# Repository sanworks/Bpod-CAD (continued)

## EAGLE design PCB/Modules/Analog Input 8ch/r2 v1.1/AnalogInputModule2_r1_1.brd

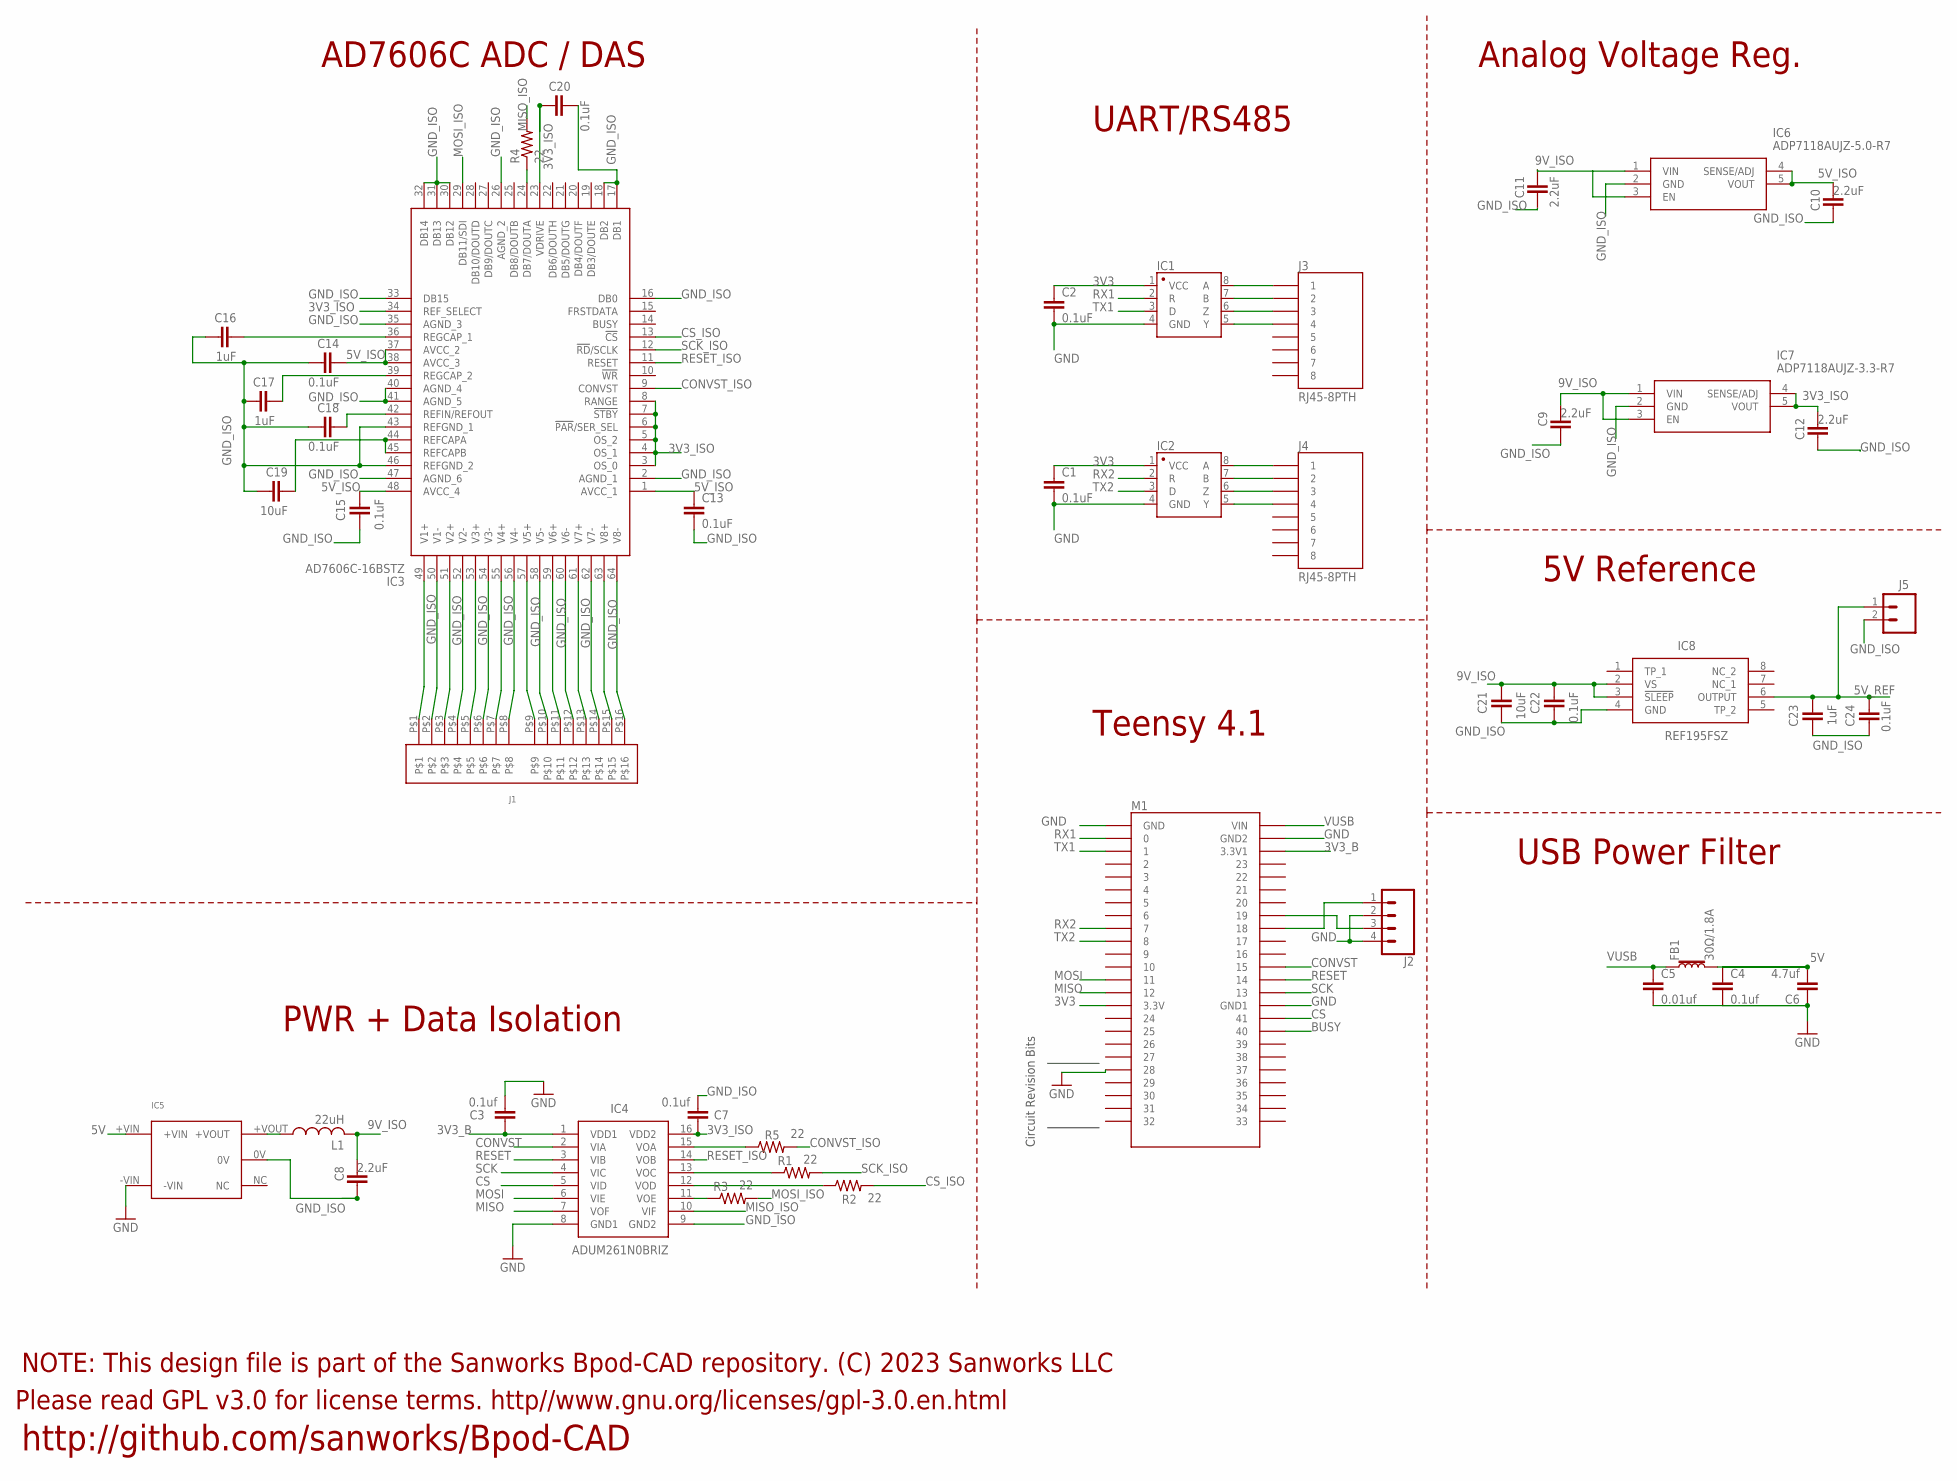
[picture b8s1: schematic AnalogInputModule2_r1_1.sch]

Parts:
C1, C2, C13, C14, C15, C18, C20, C22, C24: 0.1uF; 0805
C3, C4, C7: 0.1uf; 0805
C5: 0.01uf; 0805
C6: 4.7uf; 1206@2
C8, C9, C10, C11, C12: 2.2uF; 0805
C16, C17, C23: 1uF; 0805
C19, C21: 10uF; 0805
FB1: 30Ω/1.8A; 0603
IC1, IC2: SN65HVD31DR; SO08
IC3: AD7606C-16BSTZ; QFP50P1200X1200X160-64N
IC4: ADUM261N0BRIZ; SOIC127P1030X264-16N
IC5: 5V; MTU1D0505MC
IC6: ADP7118AUJZ-5.0-R7; SOT95P280X100-5N
IC7: ADP7118AUJZ-3.3-R7; SOT95P280X100-5N
IC8: REF195FSZ; SOIC127P600X175-8N
J1: 16POS_MOLEX_SOCKET
J2: CONN_04SCREW_LOCK; SCREWTERMINAL-3.5MM-4_LOCK
J3, J4: RJ45-8PTH; RJ45-8
J5: CONN_023.5MM_LOCK; SCREWTERMINAL-3.5MM-2_LOCK
L1: 22uH; L3225M
M1: TEENSY4.1_SIDESONLY
R1, R2, R3, R4, R5: 22; R0805

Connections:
3V3: C1.1, C2.1, IC1.1 (VCC), IC2.1 (VCC), M1.3V3 (3.3V)
3V3_B: C3.1, IC4.1 (VDD1), M1.3V3_LO (3.3V1)
3V3_ISO: C7.1, C12.2, C20.1, IC3.3 (OS_0), IC3.4 (OS_1), IC3.5 (OS_2), IC3.6 (!PAR!/SER_SEL), IC3.7 (!STBY), IC3.8 (RANGE), IC3.23 (VDRIVE), IC3.34 (REF_SELECT), IC4.16 (VDD2), IC7.4 (SENSE/ADJ), IC7.5 (VOUT)
5V: C4.1, C6.2, FB1.2, IC5.+VIN
5V_ISO: C10.2, C13.1, C14.2, C15.2, IC3.1 (AVCC_1), IC3.37 (AVCC_2), IC3.38 (AVCC_3), IC3.48 (AVCC_4), IC6.4 (SENSE/ADJ), IC6.5 (VOUT)
5V_REF: C23.2, C24.2, IC8.6 (OUTPUT), J5.1
9V_ISO: C8.2, C9.2, C11.2, C21.2, C22.2, IC6.1 (VIN), IC6.3 (EN), IC7.1 (VIN), IC7.3 (EN), IC8.2 (VS), IC8.3 (!SLEEP), L1.2
BUSY: M1.40
CONVST: IC4.2 (VIA), M1.15/A1 (15)
CONVST_ISO: IC3.9 (CONVST), R5.2
CS: IC4.5 (VID), M1.41
CS_ISO: IC3.13 (!CS), R2.2
GND: C1.2, C2.2, C3.2, C4.2, C5.2, C6.1, IC1.4 (GND), IC2.4 (GND), IC4.8 (GND1), IC5.-VIN, J2.2, J2.4, M1.28, M1.AGND (GND), M1.GND (GND1), M1.GND1 (GND2)
GND_ISO: C7.2, C8.1, C9.1, C10.1, C11.1, C12.1, C13.2, C14.1, C15.1, C16.1, C17.1, C18.1, C19.1, C20.2, C21.1, C22.1, C23.1, C24.1, IC3.2 (AGND_1), IC3.16 (DB0), IC3.17 (DB1), IC3.18 (DB2), IC3.26 (AGND_2), IC3.30 (DB12), IC3.31 (DB13), IC3.32 (DB14), IC3.33 (DB15), IC3.35 (AGND_3), IC3.40 (AGND_4), IC3.41 (AGND_5), IC3.43 (REFGND_1), IC3.46 (REFGND_2), IC3.47 (AGND_6), IC3.50 (V1-), IC3.52 (V2-), IC3.54 (V3-), IC3.56 (V4-), IC3.58 (V5-), IC3.60 (V6-), IC3.62 (V7-), IC3.64 (V8-), IC4.9 (GND2), IC5.0V, IC6.2 (GND), IC7.2 (GND), IC8.4 (GND), J1.P$2, J1.P$4, J1.P$6, J1.P$8, J1.P$10, J1.P$12, J1.P$14, J1.P$16, J5.2
MISO: IC4.7 (VOF), M1.12/MISO (12)
MISO_ISO: IC4.10 (VIF), R4.2
MOSI: IC4.6 (VIE), M1.11/MOSI (11)
MOSI_ISO: IC3.29 (DB11/SDI), R3.2
unnamed: IC1.6 (Z), J3.3
unnamed: IC1.8 (A), J3.1
unnamed: IC1.5 (Y), J3.4
unnamed: IC1.7 (B), J3.2
unnamed: IC2.6 (Z), J4.3
unnamed: IC2.5 (Y), J4.4
unnamed: IC2.8 (A), J4.1
unnamed: IC2.7 (B), J4.2
unnamed: IC3.63 (V8+), J1.P$15
unnamed: IC3.61 (V7+), J1.P$13
unnamed: IC3.59 (V6+), J1.P$11
unnamed: IC3.57 (V5+), J1.P$9
unnamed: IC3.55 (V4+), J1.P$7
unnamed: IC3.53 (V3+), J1.P$5
unnamed: IC3.51 (V2+), J1.P$3
unnamed: IC3.49 (V1+), J1.P$1
unnamed: IC4.13 (VOC), R1.1
unnamed: IC4.12 (VOD), R2.1
unnamed: IC4.11 (VOE), R3.1
unnamed: IC3.24 (DB7/DOUTA), R4.1
unnamed: IC4.15 (VOA), R5.1
unnamed: C16.2, IC3.36 (REGCAP_1)
unnamed: C17.2, IC3.39 (REGCAP_2)
unnamed: C18.2, IC3.42 (REFIN/REFOUT)
unnamed: C19.2, IC3.44 (REFCAPA), IC3.45 (REFCAPB)
unnamed: J2.1, M1.18/A4/SDA (18)
unnamed: IC5.+VOUT, L1.1
unnamed: J2.3, M1.19/A5/SCL (19)
RESET: IC4.3 (VIB), M1.14/A0 (14)
RESET_ISO: IC3.11 (RESET), IC4.14 (VOB)
RX1: IC1.2 (R), M1.0/RX (0)
RX2: IC2.2 (R), M1.7
SCK: IC4.4 (VIC), M1.13/SCK (13)
SCK_ISO: IC3.12 (!RD!/SCLK), R1.2
TX1: IC1.3 (D), M1.1/TX (1)
TX2: IC2.3 (D), M1.8
VUSB: C5.1, FB1.1, M1.VIN

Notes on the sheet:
Teensy 4.1
UART/RS485
USB Power Filter
AD7606C ADC / DAS
PWR + Data Isolation
Analog Voltage Reg.
5V Reference
Please read GPL v3.0 for license terms. http//www.gnu.org/licenses/gpl-3.0.en.html
NOTE: This design file is part of the Sanworks Bpod-CAD repository. (C) 2023 Sanworks LLC
http://github.com/sanworks/Bpod-CAD
Circuit Revision Bits

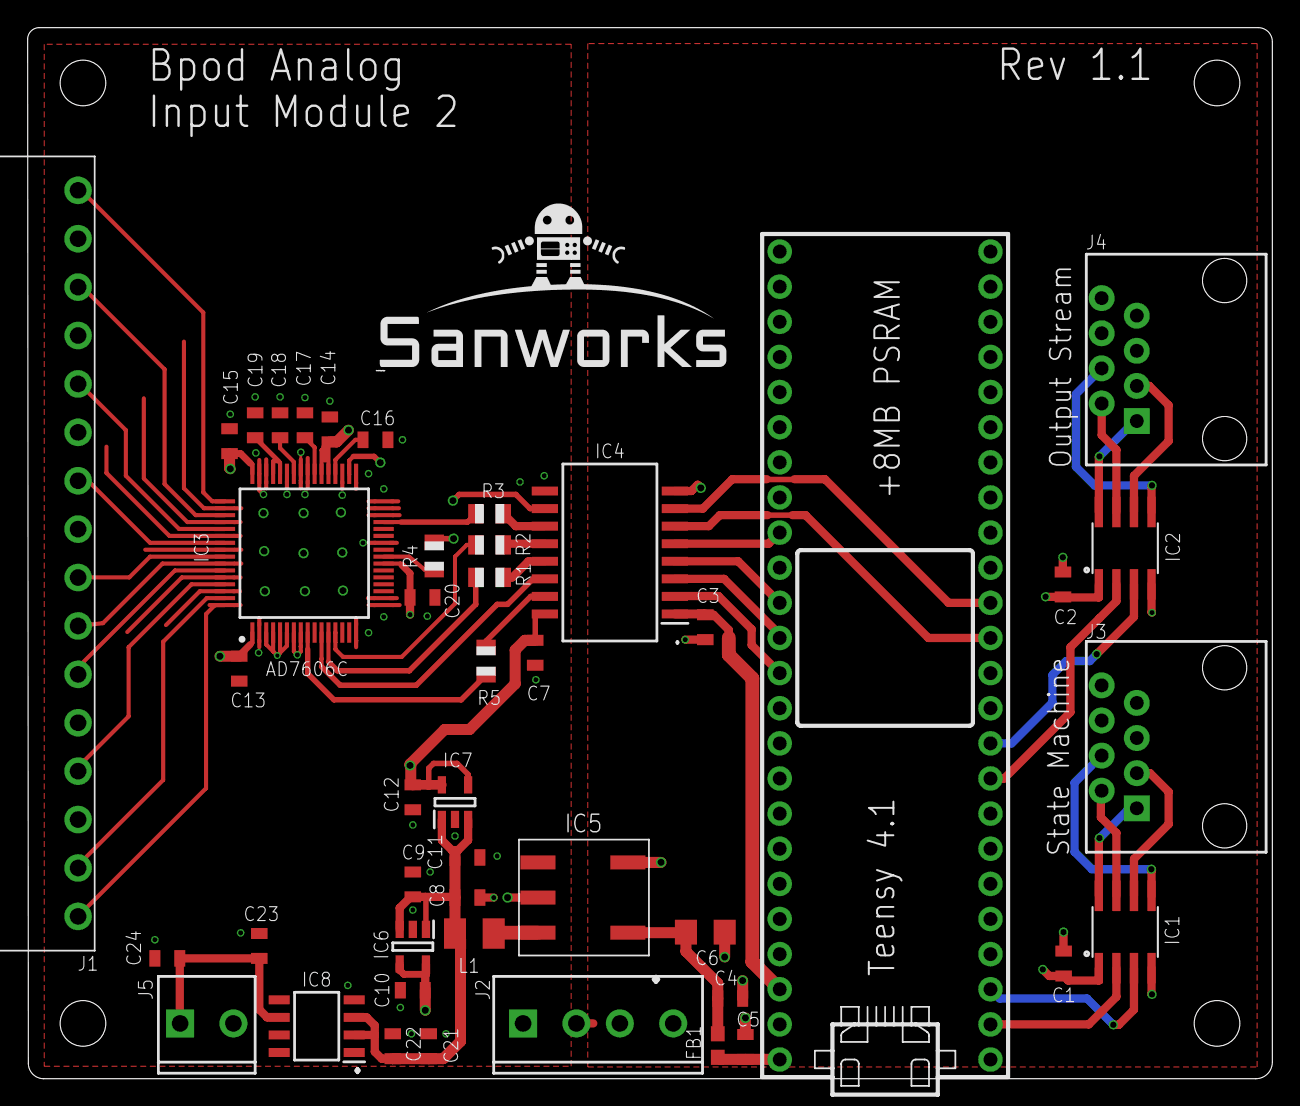
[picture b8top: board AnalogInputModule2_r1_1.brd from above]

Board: 4 copper layers, 90.0 x 76.0 mm, 50 parts (0 on the bottom side), 54 nets.

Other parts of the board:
U$1: SANWORKS_LOGO
U$5, U$6, U$7, U$8: STAND-OFF

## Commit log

2016-11-23 -Initial commit. CAD designs were previously part of the Bpod master repository.
2016-12-20 -Reorganized modules (to separate v0.5, v0.7) -Added Bpod Arduino shield for v0.7
2017-01-20 -Improved mouse box floor: increased margin between slits and floor edge, and rounded sharp corners for added mechanical strength
2017-02-01 -Added design files (PCB and enclosure) for 4-channel analog output module
2017-02-10 -Improved Analog Output Module schematic organization and labeling -Thickened trace connecting Analog Output Module ground planes
2017-03-07 -Added design files for the Pocket State Machine - a new state machine module with many improvements, based on Teensy 3.6. -Added design files for isolated valve driver module -Added new revision of 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
2017-03-07 -Added lickometer design adapted for 15-gage tubing, with sheath to protect the sensors -Added 3D printable sheets to protect bottoms of valve driver and pocket state machine boards
2017-03-08 -Added Bpod state machine PCB r0.8. Identical to r0.7 but adds isolation for BNC TTL output channels.
2017-03-10 -Updated silk screen, improved trace clearance and reorganized schematic for ValveModule PCB
2017-04-07 -Added DDS Module PCB design -Changed engraved label for clarification on analog output module enclosure
2017-04-09 -Updated analog output module PCB design
2017-04-12 -Added SNES Module PCB design -Added SNES Module bottom-guard design -Added DDS Module enclosure -Updated link to Bpod-CAD repository in schematic files
2017-05-02 - Added 8-channel analog output PCB - Updated I2C module PCB - Reorganized repository to put PCB bottom insulator designs in 1 folder -
2017-05-05 -Added improved lickometer design
2017-05-11 -Updated lickometer design, with sheath capable of mounting to a 6mm ThorLabs post.
2017-05-11 -Updated lickometer STL files
2017-07-05 -Updated 8-ch analog output module enclosure -Updated DDS module enclosure -Added 8-ch analog input module enclosure -Added 8-ch analog input module PCB
2017-07-07 -Updated DDS module PCB design. New design allows full-scale amplitude control, and has fewer components.
2017-07-10 -Added Bpod state machine r0.9 PCB files. r0.9 changes the optical isolator IC (which had been discontinued). A decoupling capacitor was added to each new optoisolator. The optoisolator series resist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
2017-08-03 -Added rotary encoder module PCB -Added 3D printable ThorLabs mount and paw-manipulation wheels for rotary encoder
2017-08-15 -Revised lickometer CAD files to improve 3D printing outcomes -Added interface board mount for 5mm acrylic (requires longer M4 screws; 20mm length up from 16mm)
2017-09-13 -Critical Update for modules with optional RJ45 power (ValveDriver, I2C, SNES and DDS); new PCB designs add a diode to prevent USB power from entering output pin of 5V regulator, when RJ45 (state mac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
2017-10-21 -Added PCB and enclosure designs for Bpod state machine v2 -Added PCB design for Bpod Teensy Shield (for Teensy 3.X) -Added RJ45 port labels on rotary encoder module PCB -Improved lickometer design -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
2017-11-27 Added a new design for lickometer with higher sensitivity
    Small modifications in the lickometer distribution that improve the sensitivity up to 18Ga.
2017-11-27 -Added revised enclosure designs for State Machine r2 + 4ch Analog Output Module, to correct for tolerance of material thickness -Added PCB design for Bpod Ethernet Module
2017-12-01 -Updated lickometer design to reduce beam size, as per contributed revision by Tiffany Ona at IDIBAPS -Updated Ethernet module enclosure design
2018-01-13 -Updated PCB designs for all boards with Teensy 3.5 + 3.6 to optimize solder pads for assembly (new designs validated 12 JAN 2018). No components changed. -Optimized silk screens on PCBs above to ens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
2018-03-26 -Added port array module PCB
2018-04-26 -Added Mouse Box v2, an improved design using thicker 4.5mm acrylic, with an acrylic base to make cleaning easier. -Added a port interface board mount for 4.5mm walls -Added a port cover (to block a 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
2018-05-03 -Added dxf files for mousebox v2 -Moved and renamed Bpod port breakout. Large, round port breakout now labeled obsolete. "Mousebox" port breakout (smt and through-hole) are the current versions, matc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
2018-05-09 -Adjusted depth of nut-cutout in mousebox v2 front foot-brackets (previous version didn't fit 4-40 nuts properly)
2018-10-02 -Added State Machine r2.2: Updated footprint for barrel jack
2019-12-19 -Added PCB files for state machine r2.3. This minor revision adds resistors to stabilize port input channels when disconnected from port interface board. (note: disconnected ports should still be dis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
2020-06-20 -Added design files for Bpod Raspberry Pi Shim -Removed references to pocket state machine
2021-06-02 -Added Bpod HiFi module PCB and enclosure CAD -Added bottom insulator sheet for port array module -Updated bottom insulator sheets for valve and I2C modules. Updated versions include spacers (previou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
2021-07-12 -Updated HiFi module PCB to v1.3. New version pulls unused channel to GND on ADUM5200 isolator, and contains silkscreen instructions for header mounting -Updated Raspberry Pi Shim to v1.1. New versio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
2022-07-09 -Added screw terminal labels for rotary encoder module v2 -Added 1x1" reference rectangle to enclosure SVG file for state machine r2 -Added laser cutting + 3D-printing design files for state machine 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
2022-07-20 -Added STL files for mouse behavior box r2
2022-09-14 -Added PCBs for State Machine r2.4 and r2.5 -Added PCB for HiFi Module r1.4 -Added PCB for Rotary Encoder Module v2
2022-10-14 -Added FSM 2+ PCB (Eagle and GERBER) files -Added updated FSM 2+ enclosure files
2022-11-21 -Added updated PCB design for FSM r2+. Version 1.2 improves regulation of the analog power supply while reducing the component count.
2023-01-23 -Added PCB files for 4ch analog output module v2
2023-03-23 -Added PCB and enclosure for Bpod Analog Input Module 2 -Updated enclosure for Analog Output Module 2 (4ch) -Reorganized Bpod modules folder -Added variant of 3D-printable wheel for mounting to 5mm s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
2023-03-24 -Updated labeling scheme for Analog Input Module 2
2023-05-04 -Added AnalogInputModule2 PCB rev1.1 -Renamed analog input module PCB folder names for clarity
2023-06-16 -Added Bpod Valve Driver Module v2 PCB and mount
2024-02-26 -State Machine PCB: Optimized through-hole sizes for alignment and solderability -Analog Output 4ch PCB: Optimized through-hole sizes for alignment and solderability, optimized DAC power rail traces 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
2024-10-28 -Added Smart Servo Module PCB + Enclosure
2025-01-16 -Bpod HiFi Module: Added circuit board v1.7. This version uses Teensy 4.1 with headers pre-installed.
2025-09-17 -Added Port Array Module v2 -Added Smart Servo Module enclosure v1.1 -Updated bottom insulator for Rotary Encoder Module v1
